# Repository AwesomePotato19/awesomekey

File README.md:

# awesomekey
building a custom keyboard!! ⌨️

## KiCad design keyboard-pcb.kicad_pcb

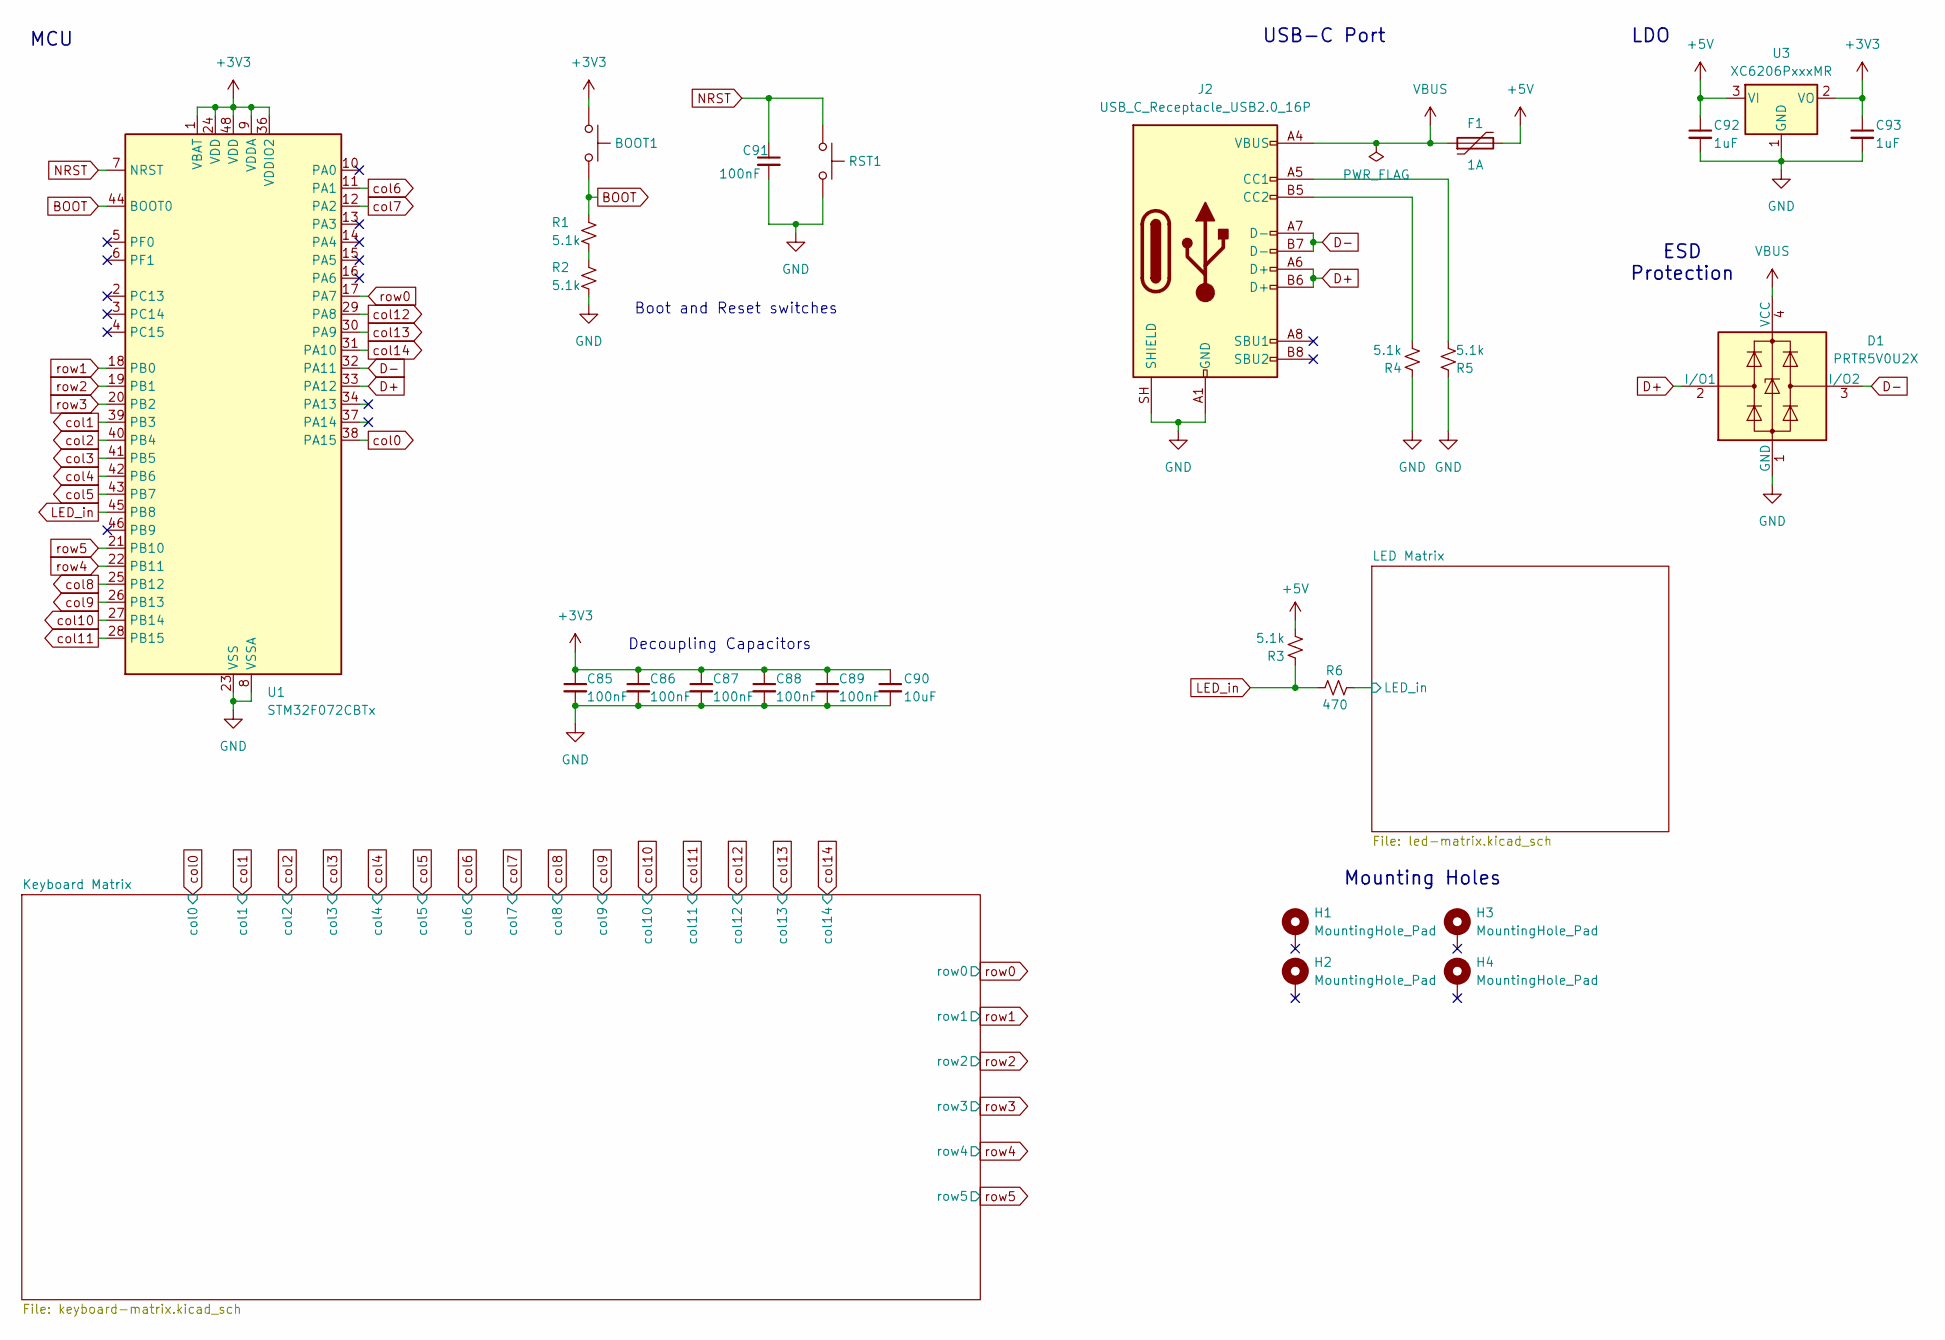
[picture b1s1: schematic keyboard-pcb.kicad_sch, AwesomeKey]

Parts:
BOOT1: BOOT; SW_SPST_TL3342
C85, C86, C87, C88, C89, C91: 100nF; C_0402_1005Metric
C90: 10uF; C_0603_1608Metric
C92, C93: 1uF; C_0603_1608Metric
D1: PRTR5V0U2X; SOT-143
F1: 1A; Fuse_1206_3216Metric
H1, H2, H3, H4: MountingHole_Pad; MountingHole_3.2mm_M3_DIN965_Pad
J2: USB_C_Receptacle_USB2.0_16P; USB_C_Receptacle_HRO_TYPE-C-31-M-12
R1, R2, R3, R4, R5: 5.1k; R_0402_1005Metric
R6: 470; R_0402_1005Metric
RST1: RESET; SW_SPST_TL3342
U1: STM32F072CBTx; LQFP-48_7x7mm_P0.5mm
U3: XC6206PxxxMR; SOT-23-3

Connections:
+3V3: BOOT1.1, C85.1, C86.1, C87.1, C88.1, C89.1, C90.1, C93.1, U1.1 (VBAT), U1.9 (VDDA), U1.24 (VDD), U1.36 (VDDIO2), U1.48 (VDD), U3.2 (VO)
+5V: C92.1, F1.2, R3.1, U3.3 (VI); also elsewhere on the board
/LED Matrix/LED_in: R6.2; also elsewhere on the board
BOOT: BOOT1.2, R1.2, U1.44 (BOOT0)
D+: D1.2 (I/O1), J2.A6 (D+), J2.B6 (D+), U1.33 (PA12)
D-: D1.3 (I/O2), J2.A7 (D-), J2.B7 (D-), U1.32 (PA11)
GND: C85.2, C86.2, C87.2, C88.2, C89.2, C90.2, C91.2, C92.2, C93.2, D1.1 (GND), J2.A1 (GND), J2.A12 (GND), J2.B1 (GND), J2.B12 (GND), J2.SH (SHIELD), R2.1, R4.2, R5.1, RST1.2, U1.8 (VSSA), U1.23 (VSS), U1.35 (VSS), U1.47 (VSS), U3.1 (GND); also elsewhere on the board
LED_in: R3.2, R6.1, U1.45 (PB8)
NRST: C91.1, RST1.1, U1.7 (NRST)
unnamed: J2.A5 (CC1), R5.2
unnamed: J2.B5 (CC2), R4.1
unnamed: R1.1, R2.2
VBUS: D1.4 (VCC), F1.1, J2.A4 (VBUS), J2.A9 (VBUS), J2.B4 (VBUS), J2.B9 (VBUS)
col0: U1.38 (PA15); also elsewhere on the board
col1: U1.39 (PB3); also elsewhere on the board
col2: U1.40 (PB4); also elsewhere on the board
col3: U1.41 (PB5); also elsewhere on the board
col4: U1.42 (PB6); also elsewhere on the board
col5: U1.43 (PB7); also elsewhere on the board
col6: U1.11 (PA1); also elsewhere on the board
col7: U1.12 (PA2); also elsewhere on the board
col8: U1.25 (PB12); also elsewhere on the board
col9: U1.26 (PB13); also elsewhere on the board
col10: U1.27 (PB14); also elsewhere on the board
col11: U1.28 (PB15); also elsewhere on the board
col12: U1.29 (PA8); also elsewhere on the board
col13: U1.30 (PA9); also elsewhere on the board
col14: U1.31 (PA10); also elsewhere on the board
row0: U1.17 (PA7); also elsewhere on the board
row1: U1.18 (PB0); also elsewhere on the board
row2: U1.19 (PB1); also elsewhere on the board
row3: U1.20 (PB2); also elsewhere on the board
row4: U1.22 (PB11); also elsewhere on the board
row5: U1.21 (PB10); also elsewhere on the board

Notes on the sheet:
LDO
Decoupling Capacitors
Mounting Holes
USB-C Port
Boot and Reset switches
MCU
ESD Protection

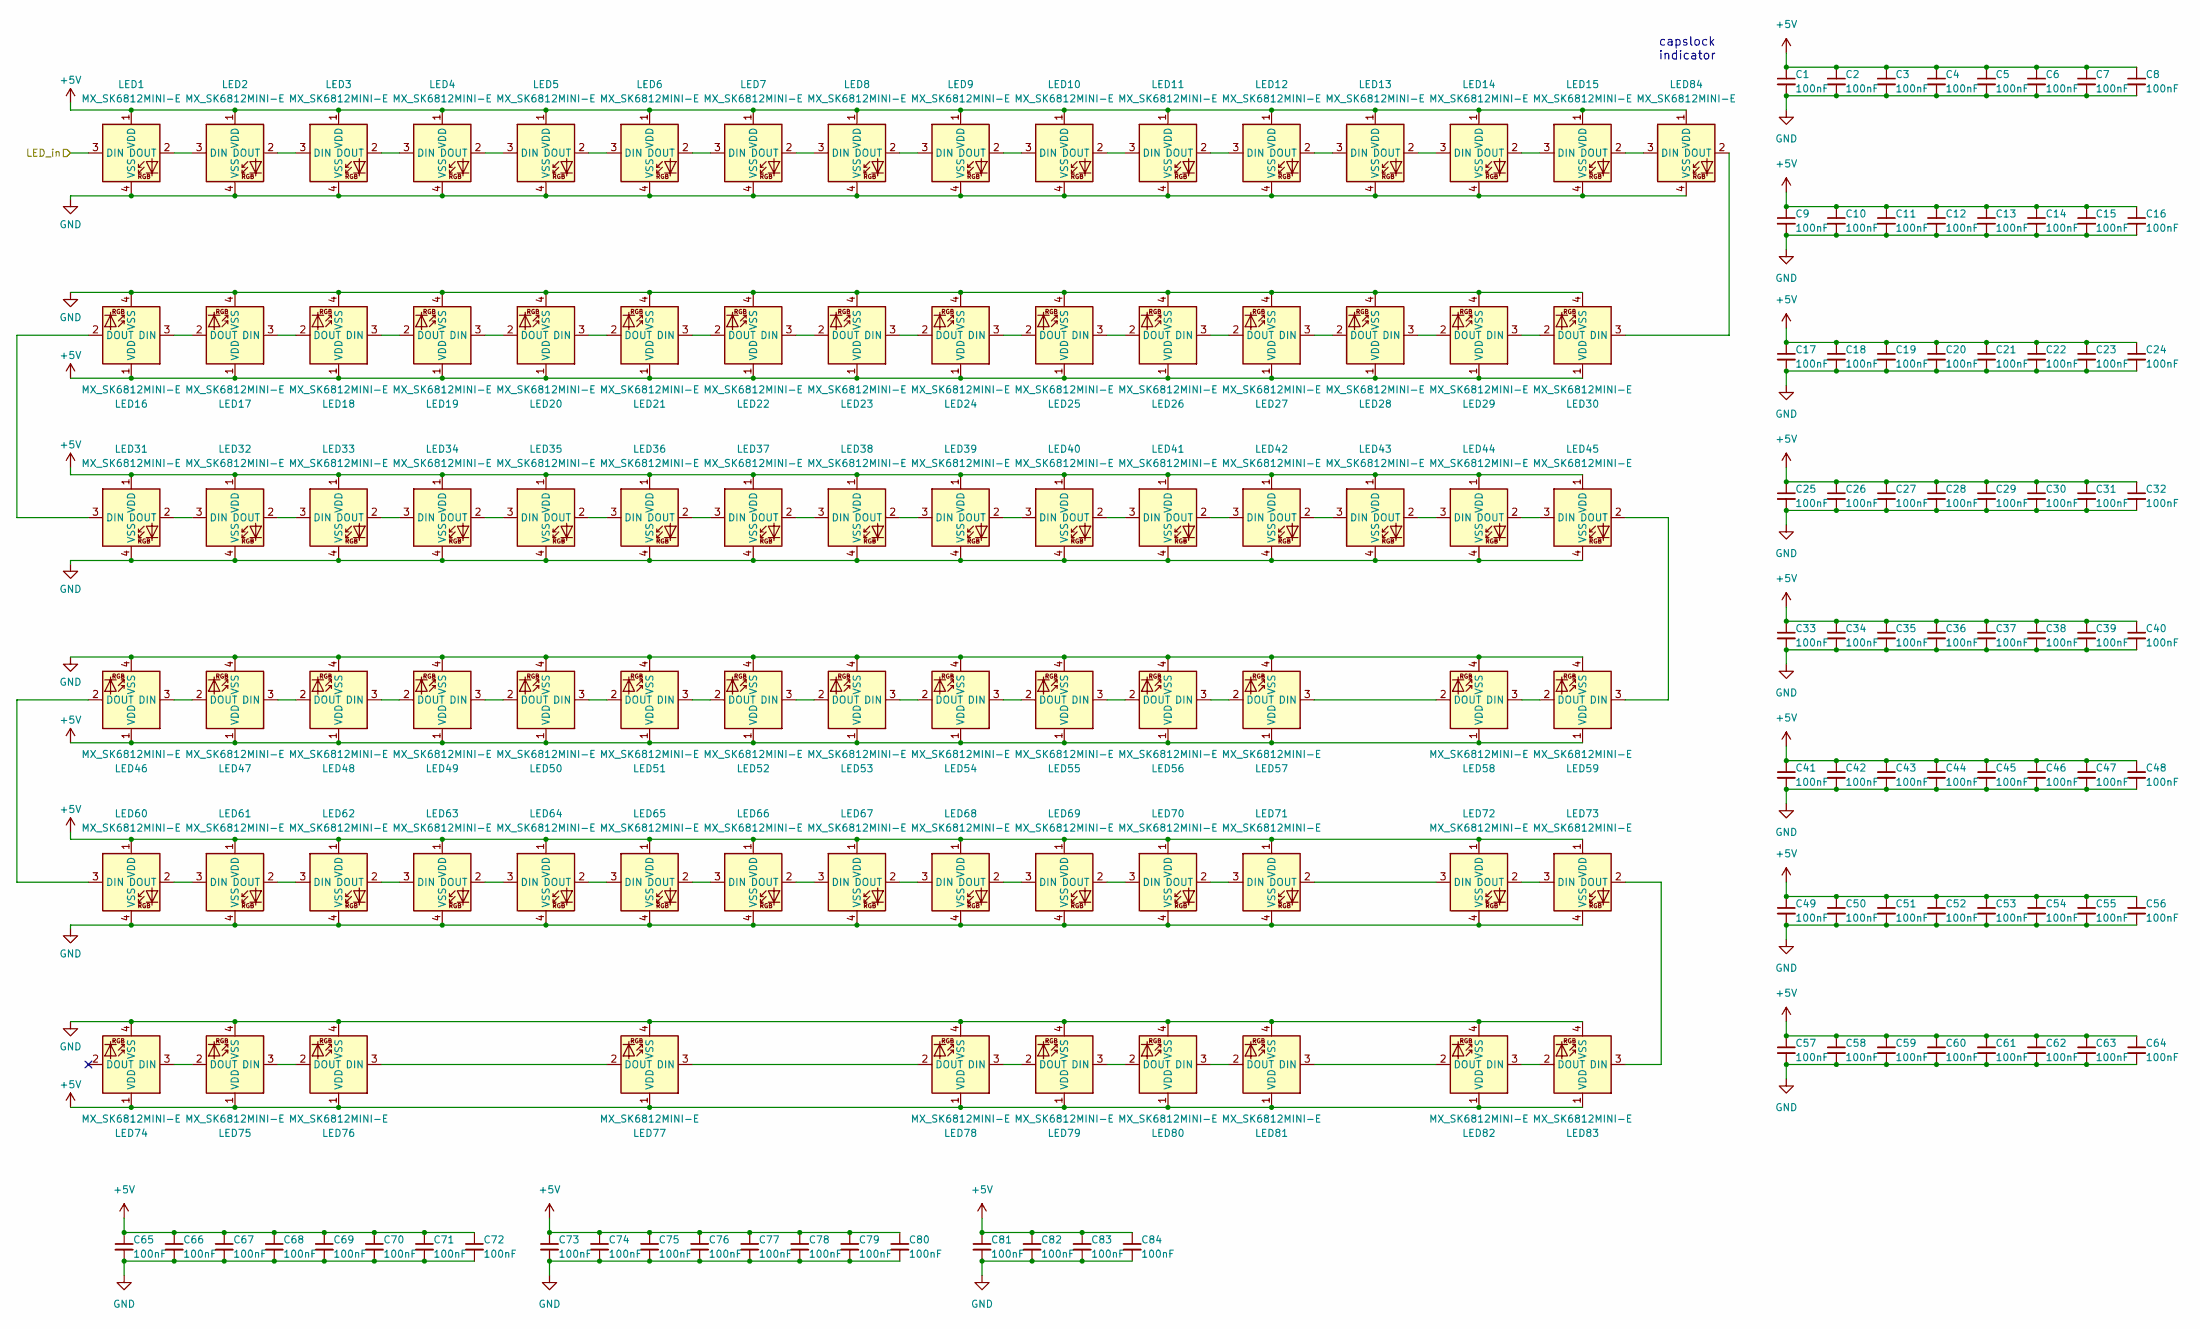
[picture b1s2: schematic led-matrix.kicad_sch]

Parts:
C1, C2, C3, C4, C5, C6, C7, C8, C9, C10, C11, C12, C13, C14, C15, C16, C17, C18, C19, C20, C21, C22, C23, C24, C25, C26, C27, C28, C29, C30, C31, C32, C33, C34, C35, C36, C37, C38, C39, C40, C41, C42, C43, C44, C45, C46, C47, C48, C49, C50, C51, C52, C53, C54, C55, C56, C57, C58, C59, C60, C61, C62, C63, C64, C65, C66, C67, C68, C69, C70, C71, C72, C73, C74, C75, C76, C77, C78, C79, C80, C81, C82, C83, C84: 100nF; C_0402_1005Metric
LED1, LED2, LED3, LED4, LED5, LED6, LED7, LED8, LED9, LED10, LED11, LED12, LED13, LED14, LED15, LED31, LED32, LED33, LED34, LED35, LED36, LED37, LED38, LED39, LED40, LED41, LED42, LED43, LED44, LED45, LED60, LED61, LED62, LED63, LED64, LED65, LED66, LED67, LED68, LED69, LED70, LED71, LED72, LED73, LED84: MX_SK6812MINI-E; LED_MX_6028R-ROT
LED16, LED17, LED18, LED19, LED20, LED21, LED22, LED23, LED24, LED25, LED26, LED27, LED28, LED29, LED30, LED46, LED47, LED48, LED49, LED50, LED51, LED52, LED53, LED54, LED55, LED56, LED57, LED58, LED59, LED74, LED75, LED76, LED77, LED78, LED79, LED80, LED81, LED82, LED83: MX_SK6812MINI-E; LED_MX_6028R

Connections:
+5V: C1.1, C2.1, C3.1, C4.1, C5.1, C6.1, C7.1, C8.1, C9.1, C10.1, C11.1, C12.1, C13.1, C14.1, C15.1, C16.1, C17.1, C18.1, C19.1, C20.1, C21.1, C22.1, C23.1, C24.1, C25.1, C26.1, C27.1, C28.1, C29.1, C30.1, C31.1, C32.1, C33.1, C34.1, C35.1, C36.1, C37.1, C38.1, C39.1, C40.1, C41.1, C42.1, C43.1, C44.1, C45.1, C46.1, C47.1, C48.1, C49.1, C50.1, C51.1, C52.1, C53.1, C54.1, C55.1, C56.1, C57.1, C58.1, C59.1, C60.1, C61.1, C62.1, C63.1, C64.1, C65.1, C66.1, C67.1, C68.1, C69.1, C70.1, C71.1, C72.1, C73.1, C74.1, C75.1, C76.1, C77.1, C78.1, C79.1, C80.1, C81.1, C82.1, C83.1, C84.1, LED1.1 (VDD), LED2.1 (VDD), LED3.1 (VDD), LED4.1 (VDD), LED5.1 (VDD), LED6.1 (VDD), LED7.1 (VDD), LED8.1 (VDD), LED9.1 (VDD), LED10.1 (VDD), LED11.1 (VDD), LED12.1 (VDD), LED13.1 (VDD), LED14.1 (VDD), LED15.1 (VDD), LED16.1 (VDD), LED17.1 (VDD), LED18.1 (VDD), LED19.1 (VDD), LED20.1 (VDD), LED21.1 (VDD), LED22.1 (VDD), LED23.1 (VDD), LED24.1 (VDD), LED25.1 (VDD), LED26.1 (VDD), LED27.1 (VDD), LED28.1 (VDD), LED29.1 (VDD), LED30.1 (VDD), LED31.1 (VDD), LED32.1 (VDD), LED33.1 (VDD), LED34.1 (VDD), LED35.1 (VDD), LED36.1 (VDD), LED37.1 (VDD), LED38.1 (VDD), LED39.1 (VDD), LED40.1 (VDD), LED41.1 (VDD), LED42.1 (VDD), LED43.1 (VDD), LED44.1 (VDD), LED45.1 (VDD), LED46.1 (VDD), LED47.1 (VDD), LED48.1 (VDD), LED49.1 (VDD), LED50.1 (VDD), LED51.1 (VDD), LED52.1 (VDD), LED53.1 (VDD), LED54.1 (VDD), LED55.1 (VDD), LED56.1 (VDD), LED57.1 (VDD), LED58.1 (VDD), LED59.1 (VDD), LED60.1 (VDD), LED61.1 (VDD), LED62.1 (VDD), LED63.1 (VDD), LED64.1 (VDD), LED65.1 (VDD), LED66.1 (VDD), LED67.1 (VDD), LED68.1 (VDD), LED69.1 (VDD), LED70.1 (VDD), LED71.1 (VDD), LED72.1 (VDD), LED73.1 (VDD), LED74.1 (VDD), LED75.1 (VDD), LED76.1 (VDD), LED77.1 (VDD), LED78.1 (VDD), LED79.1 (VDD), LED80.1 (VDD), LED81.1 (VDD), LED82.1 (VDD), LED83.1 (VDD), LED84.1 (VDD); also elsewhere on the board
/LED Matrix/LED_in: LED1.3 (DIN); also elsewhere on the board
GND: C1.2, C2.2, C3.2, C4.2, C5.2, C6.2, C7.2, C8.2, C9.2, C10.2, C11.2, C12.2, C13.2, C14.2, C15.2, C16.2, C17.2, C18.2, C19.2, C20.2, C21.2, C22.2, C23.2, C24.2, C25.2, C26.2, C27.2, C28.2, C29.2, C30.2, C31.2, C32.2, C33.2, C34.2, C35.2, C36.2, C37.2, C38.2, C39.2, C40.2, C41.2, C42.2, C43.2, C44.2, C45.2, C46.2, C47.2, C48.2, C49.2, C50.2, C51.2, C52.2, C53.2, C54.2, C55.2, C56.2, C57.2, C58.2, C59.2, C60.2, C61.2, C62.2, C63.2, C64.2, C65.2, C66.2, C67.2, C68.2, C69.2, C70.2, C71.2, C72.2, C73.2, C74.2, C75.2, C76.2, C77.2, C78.2, C79.2, C80.2, C81.2, C82.2, C83.2, C84.2, LED1.4 (VSS), LED2.4 (VSS), LED3.4 (VSS), LED4.4 (VSS), LED5.4 (VSS), LED6.4 (VSS), LED7.4 (VSS), LED8.4 (VSS), LED9.4 (VSS), LED10.4 (VSS), LED11.4 (VSS), LED12.4 (VSS), LED13.4 (VSS), LED14.4 (VSS), LED15.4 (VSS), LED16.4 (VSS), LED17.4 (VSS), LED18.4 (VSS), LED19.4 (VSS), LED20.4 (VSS), LED21.4 (VSS), LED22.4 (VSS), LED23.4 (VSS), LED24.4 (VSS), LED25.4 (VSS), LED26.4 (VSS), LED27.4 (VSS), LED28.4 (VSS), LED29.4 (VSS), LED30.4 (VSS), LED31.4 (VSS), LED32.4 (VSS), LED33.4 (VSS), LED34.4 (VSS), LED35.4 (VSS), LED36.4 (VSS), LED37.4 (VSS), LED38.4 (VSS), LED39.4 (VSS), LED40.4 (VSS), LED41.4 (VSS), LED42.4 (VSS), LED43.4 (VSS), LED44.4 (VSS), LED45.4 (VSS), LED46.4 (VSS), LED47.4 (VSS), LED48.4 (VSS), LED49.4 (VSS), LED50.4 (VSS), LED51.4 (VSS), LED52.4 (VSS), LED53.4 (VSS), LED54.4 (VSS), LED55.4 (VSS), LED56.4 (VSS), LED57.4 (VSS), LED58.4 (VSS), LED59.4 (VSS), LED60.4 (VSS), LED61.4 (VSS), LED62.4 (VSS), LED63.4 (VSS), LED64.4 (VSS), LED65.4 (VSS), LED66.4 (VSS), LED67.4 (VSS), LED68.4 (VSS), LED69.4 (VSS), LED70.4 (VSS), LED71.4 (VSS), LED72.4 (VSS), LED73.4 (VSS), LED74.4 (VSS), LED75.4 (VSS), LED76.4 (VSS), LED77.4 (VSS), LED78.4 (VSS), LED79.4 (VSS), LED80.4 (VSS), LED81.4 (VSS), LED82.4 (VSS), LED83.4 (VSS), LED84.4 (VSS); also elsewhere on the board
unnamed: LED1.2 (DOUT), LED2.3 (DIN)
unnamed: LED2.2 (DOUT), LED3.3 (DIN)
unnamed: LED3.2 (DOUT), LED4.3 (DIN)
unnamed: LED4.2 (DOUT), LED5.3 (DIN)
unnamed: LED5.2 (DOUT), LED6.3 (DIN)
unnamed: LED6.2 (DOUT), LED7.3 (DIN)
unnamed: LED7.2 (DOUT), LED8.3 (DIN)
unnamed: LED8.2 (DOUT), LED9.3 (DIN)
unnamed: LED9.2 (DOUT), LED10.3 (DIN)
unnamed: LED10.2 (DOUT), LED11.3 (DIN)
unnamed: LED11.2 (DOUT), LED12.3 (DIN)
unnamed: LED12.2 (DOUT), LED13.3 (DIN)
unnamed: LED13.2 (DOUT), LED14.3 (DIN)
unnamed: LED14.2 (DOUT), LED15.3 (DIN)
unnamed: LED15.2 (DOUT), LED84.3 (DIN)
unnamed: LED16.3 (DIN), LED17.2 (DOUT)
unnamed: LED16.2 (DOUT), LED31.3 (DIN)
unnamed: LED17.3 (DIN), LED18.2 (DOUT)
unnamed: LED18.3 (DIN), LED19.2 (DOUT)
unnamed: LED19.3 (DIN), LED20.2 (DOUT)
unnamed: LED20.3 (DIN), LED21.2 (DOUT)
unnamed: LED21.3 (DIN), LED22.2 (DOUT)
unnamed: LED22.3 (DIN), LED23.2 (DOUT)
unnamed: LED23.3 (DIN), LED24.2 (DOUT)
unnamed: LED24.3 (DIN), LED25.2 (DOUT)
unnamed: LED25.3 (DIN), LED26.2 (DOUT)
unnamed: LED26.3 (DIN), LED27.2 (DOUT)
unnamed: LED27.3 (DIN), LED28.2 (DOUT)
unnamed: LED28.3 (DIN), LED29.2 (DOUT)
unnamed: LED29.3 (DIN), LED30.2 (DOUT)
unnamed: LED30.3 (DIN), LED84.2 (DOUT)
unnamed: LED31.2 (DOUT), LED32.3 (DIN)
unnamed: LED32.2 (DOUT), LED33.3 (DIN)
unnamed: LED33.2 (DOUT), LED34.3 (DIN)
unnamed: LED34.2 (DOUT), LED35.3 (DIN)
unnamed: LED35.2 (DOUT), LED36.3 (DIN)
unnamed: LED36.2 (DOUT), LED37.3 (DIN)
unnamed: LED37.2 (DOUT), LED38.3 (DIN)
unnamed: LED38.2 (DOUT), LED39.3 (DIN)
unnamed: LED39.2 (DOUT), LED40.3 (DIN)
unnamed: LED40.2 (DOUT), LED41.3 (DIN)
unnamed: LED41.2 (DOUT), LED42.3 (DIN)
unnamed: LED42.2 (DOUT), LED43.3 (DIN)
unnamed: LED43.2 (DOUT), LED44.3 (DIN)
unnamed: LED44.2 (DOUT), LED45.3 (DIN)
unnamed: LED45.2 (DOUT), LED59.3 (DIN)
unnamed: LED46.3 (DIN), LED47.2 (DOUT)
unnamed: LED46.2 (DOUT), LED60.3 (DIN)
unnamed: LED47.3 (DIN), LED48.2 (DOUT)
unnamed: LED48.3 (DIN), LED49.2 (DOUT)
unnamed: LED49.3 (DIN), LED50.2 (DOUT)
unnamed: LED50.3 (DIN), LED51.2 (DOUT)
unnamed: LED51.3 (DIN), LED52.2 (DOUT)
unnamed: LED52.3 (DIN), LED53.2 (DOUT)
unnamed: LED53.3 (DIN), LED54.2 (DOUT)
unnamed: LED54.3 (DIN), LED55.2 (DOUT)
unnamed: LED55.3 (DIN), LED56.2 (DOUT)
unnamed: LED56.3 (DIN), LED57.2 (DOUT)
unnamed: LED57.3 (DIN), LED58.2 (DOUT)
unnamed: LED58.3 (DIN), LED59.2 (DOUT)
unnamed: LED60.2 (DOUT), LED61.3 (DIN)
unnamed: LED61.2 (DOUT), LED62.3 (DIN)
unnamed: LED62.2 (DOUT), LED63.3 (DIN)
unnamed: LED63.2 (DOUT), LED64.3 (DIN)
unnamed: LED64.2 (DOUT), LED65.3 (DIN)
unnamed: LED65.2 (DOUT), LED66.3 (DIN)
unnamed: LED66.2 (DOUT), LED67.3 (DIN)
unnamed: LED67.2 (DOUT), LED68.3 (DIN)
unnamed: LED68.2 (DOUT), LED69.3 (DIN)
unnamed: LED69.2 (DOUT), LED70.3 (DIN)
unnamed: LED70.2 (DOUT), LED71.3 (DIN)
unnamed: LED71.2 (DOUT), LED72.3 (DIN)
unnamed: LED72.2 (DOUT), LED73.3 (DIN)
unnamed: LED73.2 (DOUT), LED83.3 (DIN)
unnamed: LED74.3 (DIN), LED75.2 (DOUT)
unnamed: LED75.3 (DIN), LED76.2 (DOUT)
unnamed: LED76.3 (DIN), LED77.2 (DOUT)
unnamed: LED77.3 (DIN), LED78.2 (DOUT)
unnamed: LED78.3 (DIN), LED79.2 (DOUT)
unnamed: LED79.3 (DIN), LED80.2 (DOUT)
unnamed: LED80.3 (DIN), LED81.2 (DOUT)
unnamed: LED81.3 (DIN), LED82.2 (DOUT)
unnamed: LED82.3 (DIN), LED83.2 (DOUT)

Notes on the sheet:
capslock indicator

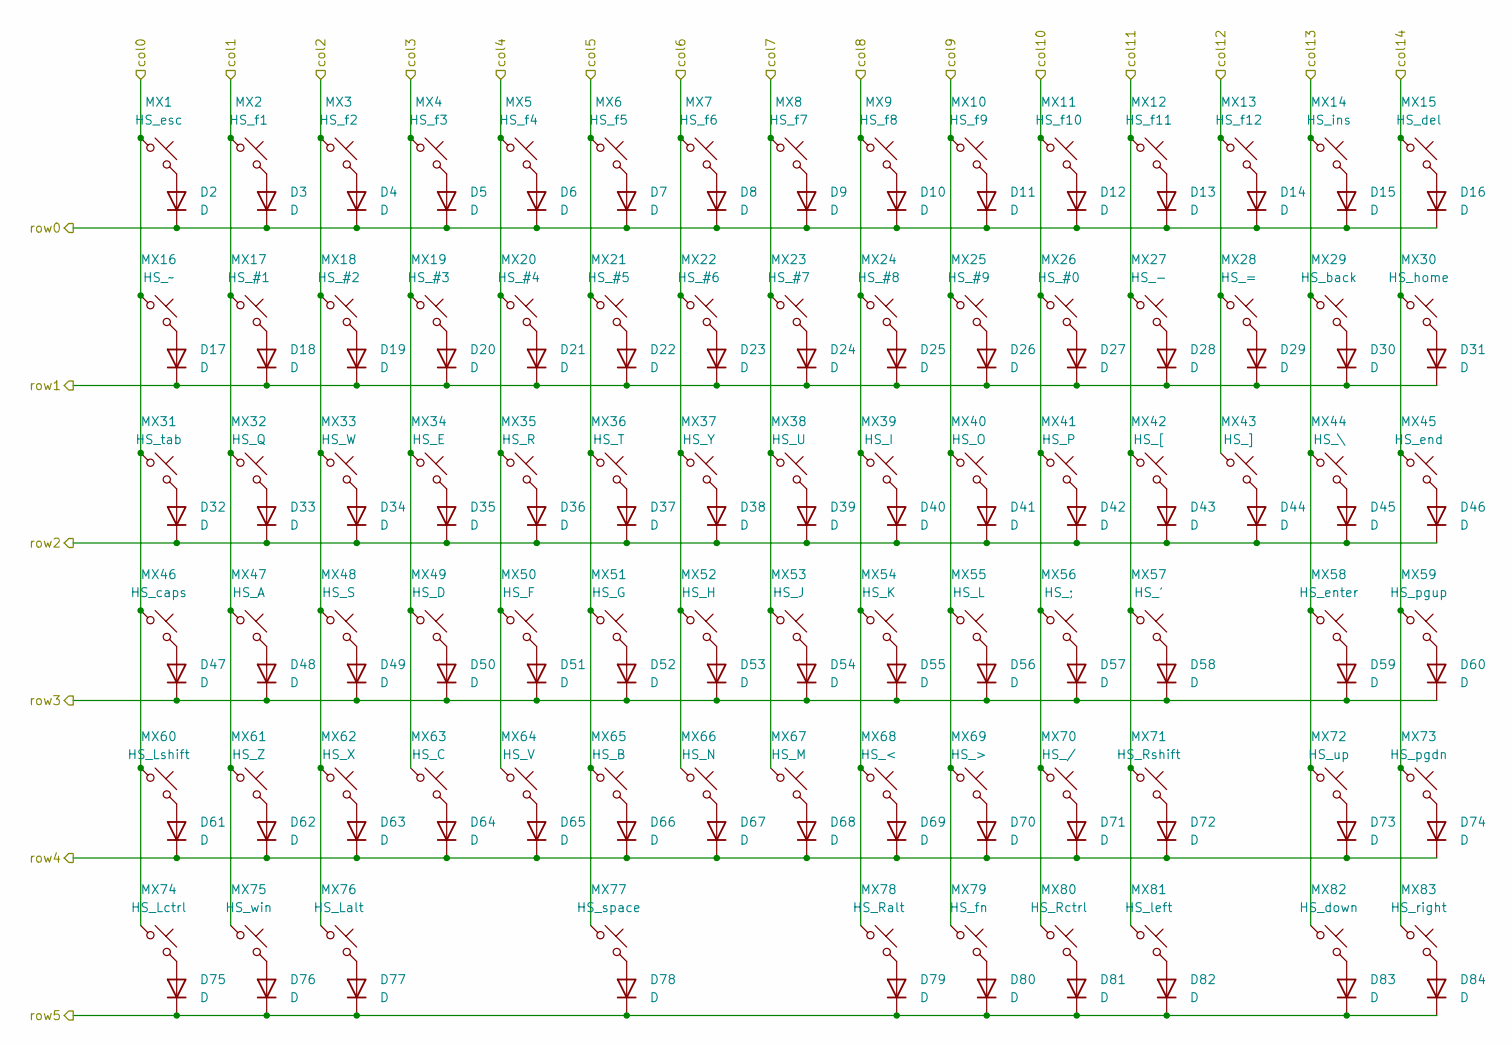
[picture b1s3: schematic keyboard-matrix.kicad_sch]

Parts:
D2, D3, D4, D5, D6, D7, D8, D9, D10, D11, D12, D13, D14, D15, D16, D17, D18, D19, D20, D21, D22, D23, D24, D25, D26, D27, D28, D29, D30, D31, D32, D33, D34, D35, D36, D37, D38, D39, D40, D41, D42, D43, D44, D45, D46, D47, D48, D49, D50, D51, D52, D53, D54, D55, D56, D57, D58, D59, D60, D61, D62, D63, D64, D65, D66, D67, D68, D69, D70, D71, D72, D73, D74, D75, D76, D77, D78, D79, D80, D81, D82, D83, D84: D; D_SOD-123
MX1: HS_esc; MX-Hotswap-1U
MX2: HS_f1; MX-Hotswap-1U
MX3: HS_f2; MX-Hotswap-1U
MX4: HS_f3; MX-Hotswap-1U
MX5: HS_f4; MX-Hotswap-1U
MX6: HS_f5; MX-Hotswap-1U
MX7: HS_f6; MX-Hotswap-1U
MX8: HS_f7; MX-Hotswap-1U
MX9: HS_f8; MX-Hotswap-1U
MX10: HS_f9; MX-Hotswap-1U
MX11: HS_f10; MX-Hotswap-1U
MX12: HS_f11; MX-Hotswap-1U
MX13: HS_f12; MX-Hotswap-1U
MX14: HS_ins; MX-Hotswap-1U
MX15: HS_del; MX-Hotswap-1U
MX16: HS_~; MX-Hotswap-1U
MX17: HS_#1; MX-Hotswap-1U
MX18: HS_#2; MX-Hotswap-1U
MX19: HS_#3; MX-Hotswap-1U
MX20: HS_#4; MX-Hotswap-1U
MX21: HS_#5; MX-Hotswap-1U
MX22: HS_#6; MX-Hotswap-1U
MX23: HS_#7; MX-Hotswap-1U
MX24: HS_#8; MX-Hotswap-1U
MX25: HS_#9; MX-Hotswap-1U
MX26: HS_#0; MX-Hotswap-1U
MX27: HS_-; MX-Hotswap-1U
MX28: HS_=; MX-Hotswap-1U
MX29: HS_back; MX-Hotswap-2U
MX30: HS_home; MX-Hotswap-1U
MX31: HS_tab; MX-Hotswap-1.5U
MX32: HS_Q; MX-Hotswap-1U
MX33: HS_W; MX-Hotswap-1U
MX34: HS_E; MX-Hotswap-1U
MX35: HS_R; MX-Hotswap-1U
MX36: HS_T; MX-Hotswap-1U
MX37: HS_Y; MX-Hotswap-1U
MX38: HS_U; MX-Hotswap-1U
MX39: HS_I; MX-Hotswap-1U
MX40: HS_O; MX-Hotswap-1U
MX41: HS_P; MX-Hotswap-1U
MX42: HS_[; MX-Hotswap-1U
MX43: HS_]; MX-Hotswap-1U
MX44: HS_\; MX-Hotswap-1U
MX45: HS_end; MX-Hotswap-1U
MX46: HS_caps; MX-Hotswap-1.75U
MX47: HS_A; MX-Hotswap-1U
MX48: HS_S; MX-Hotswap-1U
MX49: HS_D; MX-Hotswap-1U
MX50: HS_F; MX-Hotswap-1U
MX51: HS_G; MX-Hotswap-1U
MX52: HS_H; MX-Hotswap-1U
MX53: HS_J; MX-Hotswap-1U
MX54: HS_K; MX-Hotswap-1U
MX55: HS_L; MX-Hotswap-1U
MX56: HS_;; MX-Hotswap-1U
MX57: HS_'; MX-Hotswap-1U
MX58: HS_enter; MX-Hotswap-2.25U
MX59: HS_pgup; MX-Hotswap-1U
MX60: HS_Lshift; MX-Hotswap-2.25U
MX61: HS_Z; MX-Hotswap-1U
MX62: HS_X; MX-Hotswap-1U
MX63: HS_C; MX-Hotswap-1U
MX64: HS_V; MX-Hotswap-1U
MX65: HS_B; MX-Hotswap-1U
MX66: HS_N; MX-Hotswap-1U
MX67: HS_M; MX-Hotswap-1U
MX68: HS_<; MX-Hotswap-1U
MX69: HS_>; MX-Hotswap-1U
MX70: HS_/; MX-Hotswap-1U
MX71: HS_Rshift; MX-Hotswap-1U
MX72: HS_up; MX-Hotswap-1U
MX73: HS_pgdn; MX-Hotswap-1U
MX74: HS_Lctrl; MX-Hotswap-1.25U
MX75: HS_win; MX-Hotswap-1.25U
MX76: HS_Lalt; MX-Hotswap-1.25U
MX77: HS_space; MX-Hotswap-6.25U-ReversedStabilizers
MX78: HS_Ralt; MX-Hotswap-1U
MX79: HS_fn; MX-Hotswap-1U
MX80: HS_Rctrl; MX-Hotswap-1U
MX81: HS_left; MX-Hotswap-1U
MX82: HS_down; MX-Hotswap-1U
MX83: HS_right; MX-Hotswap-1U

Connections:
unnamed: D2.2 (A), MX1.2
unnamed: D3.2 (A), MX2.2
unnamed: D4.2 (A), MX3.2
unnamed: D5.2 (A), MX4.2
unnamed: D6.2 (A), MX5.2
unnamed: D7.2 (A), MX6.2
unnamed: D8.2 (A), MX7.2
unnamed: D9.2 (A), MX8.2
unnamed: D10.2 (A), MX9.2
unnamed: D11.2 (A), MX10.2
unnamed: D12.2 (A), MX11.2
unnamed: D13.2 (A), MX12.2
unnamed: D14.2 (A), MX13.2
unnamed: D15.2 (A), MX14.2
unnamed: D16.2 (A), MX15.2
unnamed: D17.2 (A), MX16.2
unnamed: D18.2 (A), MX17.2
unnamed: D19.2 (A), MX18.2
unnamed: D20.2 (A), MX19.2
unnamed: D21.2 (A), MX20.2
unnamed: D22.2 (A), MX21.2
unnamed: D23.2 (A), MX22.2
unnamed: D24.2 (A), MX23.2
unnamed: D25.2 (A), MX24.2
unnamed: D26.2 (A), MX25.2
unnamed: D27.2 (A), MX26.2
unnamed: D28.2 (A), MX27.2
unnamed: D29.2 (A), MX28.2
unnamed: D30.2 (A), MX29.2
unnamed: D31.2 (A), MX30.2
unnamed: D32.2 (A), MX31.2
unnamed: D33.2 (A), MX32.2
unnamed: D34.2 (A), MX33.2
unnamed: D35.2 (A), MX34.2
unnamed: D36.2 (A), MX35.2
unnamed: D37.2 (A), MX36.2
unnamed: D38.2 (A), MX37.2
unnamed: D39.2 (A), MX38.2
unnamed: D40.2 (A), MX39.2
unnamed: D41.2 (A), MX40.2
unnamed: D42.2 (A), MX41.2
unnamed: D43.2 (A), MX42.2
unnamed: D44.2 (A), MX43.2
unnamed: D45.2 (A), MX44.2
unnamed: D46.2 (A), MX45.2
unnamed: D47.2 (A), MX46.2
unnamed: D48.2 (A), MX47.2
unnamed: D49.2 (A), MX48.2
unnamed: D50.2 (A), MX49.2
unnamed: D51.2 (A), MX50.2
unnamed: D52.2 (A), MX51.2
unnamed: D53.2 (A), MX52.2
unnamed: D54.2 (A), MX53.2
unnamed: D55.2 (A), MX54.2
unnamed: D56.2 (A), MX55.2
unnamed: D57.2 (A), MX56.2
unnamed: D58.2 (A), MX57.2
unnamed: D59.2 (A), MX58.2
unnamed: D60.2 (A), MX59.2
unnamed: D61.2 (A), MX60.2
unnamed: D62.2 (A), MX61.2
unnamed: D63.2 (A), MX62.2
unnamed: D64.2 (A), MX63.2
unnamed: D65.2 (A), MX64.2
unnamed: D66.2 (A), MX65.2
unnamed: D67.2 (A), MX66.2
unnamed: D68.2 (A), MX67.2
unnamed: D69.2 (A), MX68.2
unnamed: D70.2 (A), MX69.2
unnamed: D71.2 (A), MX70.2
unnamed: D72.2 (A), MX71.2
unnamed: D73.2 (A), MX72.2
unnamed: D74.2 (A), MX73.2
unnamed: D75.2 (A), MX74.2
unnamed: D76.2 (A), MX75.2
unnamed: D77.2 (A), MX76.2
unnamed: D78.2 (A), MX77.2
unnamed: D79.2 (A), MX78.2
unnamed: D80.2 (A), MX79.2
unnamed: D81.2 (A), MX80.2
unnamed: D82.2 (A), MX81.2
unnamed: D83.2 (A), MX82.2
unnamed: D84.2 (A), MX83.2
col0: MX1.1, MX16.1, MX31.1, MX46.1, MX60.1, MX74.1; also elsewhere on the board
col1: MX2.1, MX17.1, MX32.1, MX47.1, MX61.1, MX75.1; also elsewhere on the board
col2: MX3.1, MX18.1, MX33.1, MX48.1, MX62.1, MX76.1; also elsewhere on the board
col3: MX4.1, MX19.1, MX34.1, MX49.1, MX63.1; also elsewhere on the board
col4: MX5.1, MX20.1, MX35.1, MX50.1, MX64.1; also elsewhere on the board
col5: MX6.1, MX21.1, MX36.1, MX51.1, MX65.1, MX77.1; also elsewhere on the board
col6: MX7.1, MX22.1, MX37.1, MX52.1, MX66.1; also elsewhere on the board
col7: MX8.1, MX23.1, MX38.1, MX53.1, MX67.1; also elsewhere on the board
col8: MX9.1, MX24.1, MX39.1, MX54.1, MX68.1, MX78.1; also elsewhere on the board
col9: MX10.1, MX25.1, MX40.1, MX55.1, MX69.1, MX79.1; also elsewhere on the board
col10: MX11.1, MX26.1, MX41.1, MX56.1, MX70.1, MX80.1; also elsewhere on the board
col11: MX12.1, MX27.1, MX42.1, MX57.1, MX71.1, MX81.1; also elsewhere on the board
col12: MX13.1, MX28.1, MX43.1; also elsewhere on the board
col13: MX14.1, MX29.1, MX44.1, MX58.1, MX72.1, MX82.1; also elsewhere on the board
col14: MX15.1, MX30.1, MX45.1, MX59.1, MX73.1, MX83.1; also elsewhere on the board
row0: D2.1 (K), D3.1 (K), D4.1 (K), D5.1 (K), D6.1 (K), D7.1 (K), D8.1 (K), D9.1 (K), D10.1 (K), D11.1 (K), D12.1 (K), D13.1 (K), D14.1 (K), D15.1 (K), D16.1 (K); also elsewhere on the board
row1: D17.1 (K), D18.1 (K), D19.1 (K), D20.1 (K), D21.1 (K), D22.1 (K), D23.1 (K), D24.1 (K), D25.1 (K), D26.1 (K), D27.1 (K), D28.1 (K), D29.1 (K), D30.1 (K), D31.1 (K); also elsewhere on the board
row2: D32.1 (K), D33.1 (K), D34.1 (K), D35.1 (K), D36.1 (K), D37.1 (K), D38.1 (K), D39.1 (K), D40.1 (K), D41.1 (K), D42.1 (K), D43.1 (K), D44.1 (K), D45.1 (K), D46.1 (K); also elsewhere on the board
row3: D47.1 (K), D48.1 (K), D49.1 (K), D50.1 (K), D51.1 (K), D52.1 (K), D53.1 (K), D54.1 (K), D55.1 (K), D56.1 (K), D57.1 (K), D58.1 (K), D59.1 (K), D60.1 (K); also elsewhere on the board
row4: D61.1 (K), D62.1 (K), D63.1 (K), D64.1 (K), D65.1 (K), D66.1 (K), D67.1 (K), D68.1 (K), D69.1 (K), D70.1 (K), D71.1 (K), D72.1 (K), D73.1 (K), D74.1 (K); also elsewhere on the board
row5: D75.1 (K), D76.1 (K), D77.1 (K), D78.1 (K), D79.1 (K), D80.1 (K), D81.1 (K), D82.1 (K), D83.1 (K), D84.1 (K); also elsewhere on the board

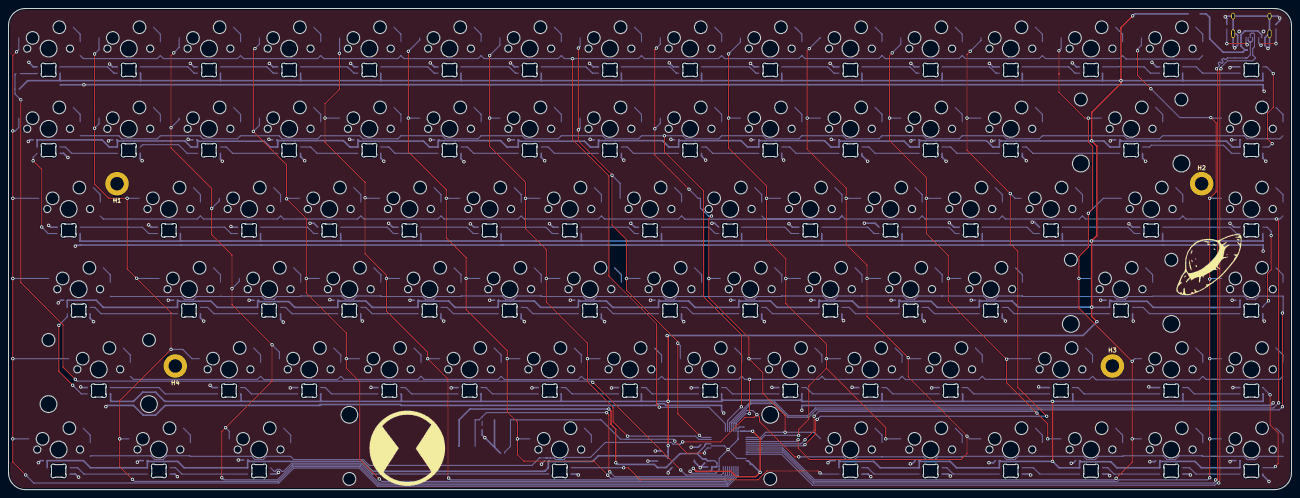
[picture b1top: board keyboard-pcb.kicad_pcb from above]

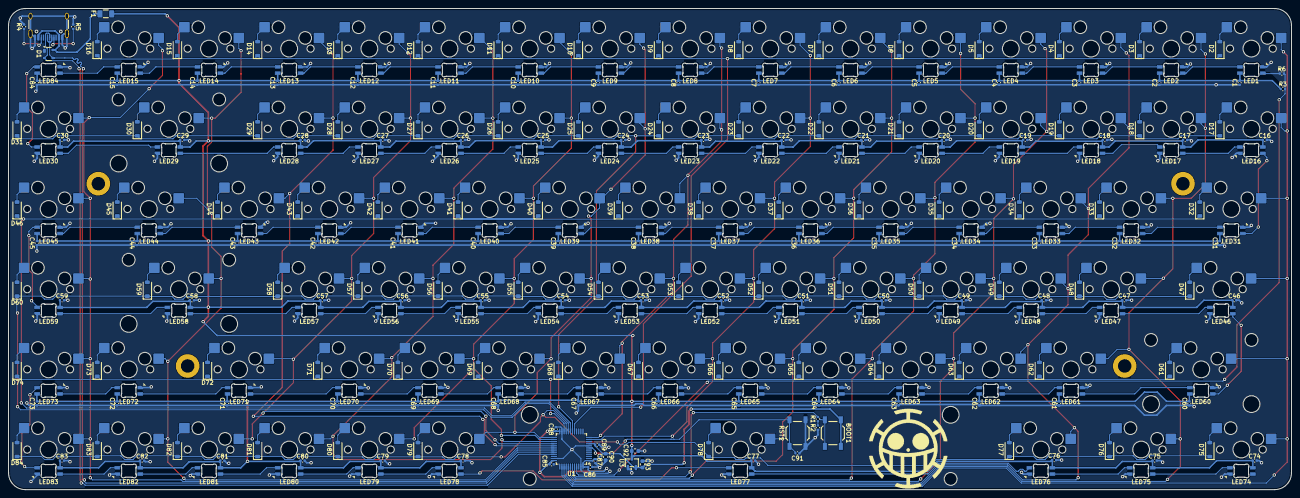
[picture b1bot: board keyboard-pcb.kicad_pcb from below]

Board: 2 copper layers, 304.8 x 114.3 mm, 360 parts (356 on the bottom side), 200 nets.
